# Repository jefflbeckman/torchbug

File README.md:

torchbug
========

Thingsquare application for LED poi

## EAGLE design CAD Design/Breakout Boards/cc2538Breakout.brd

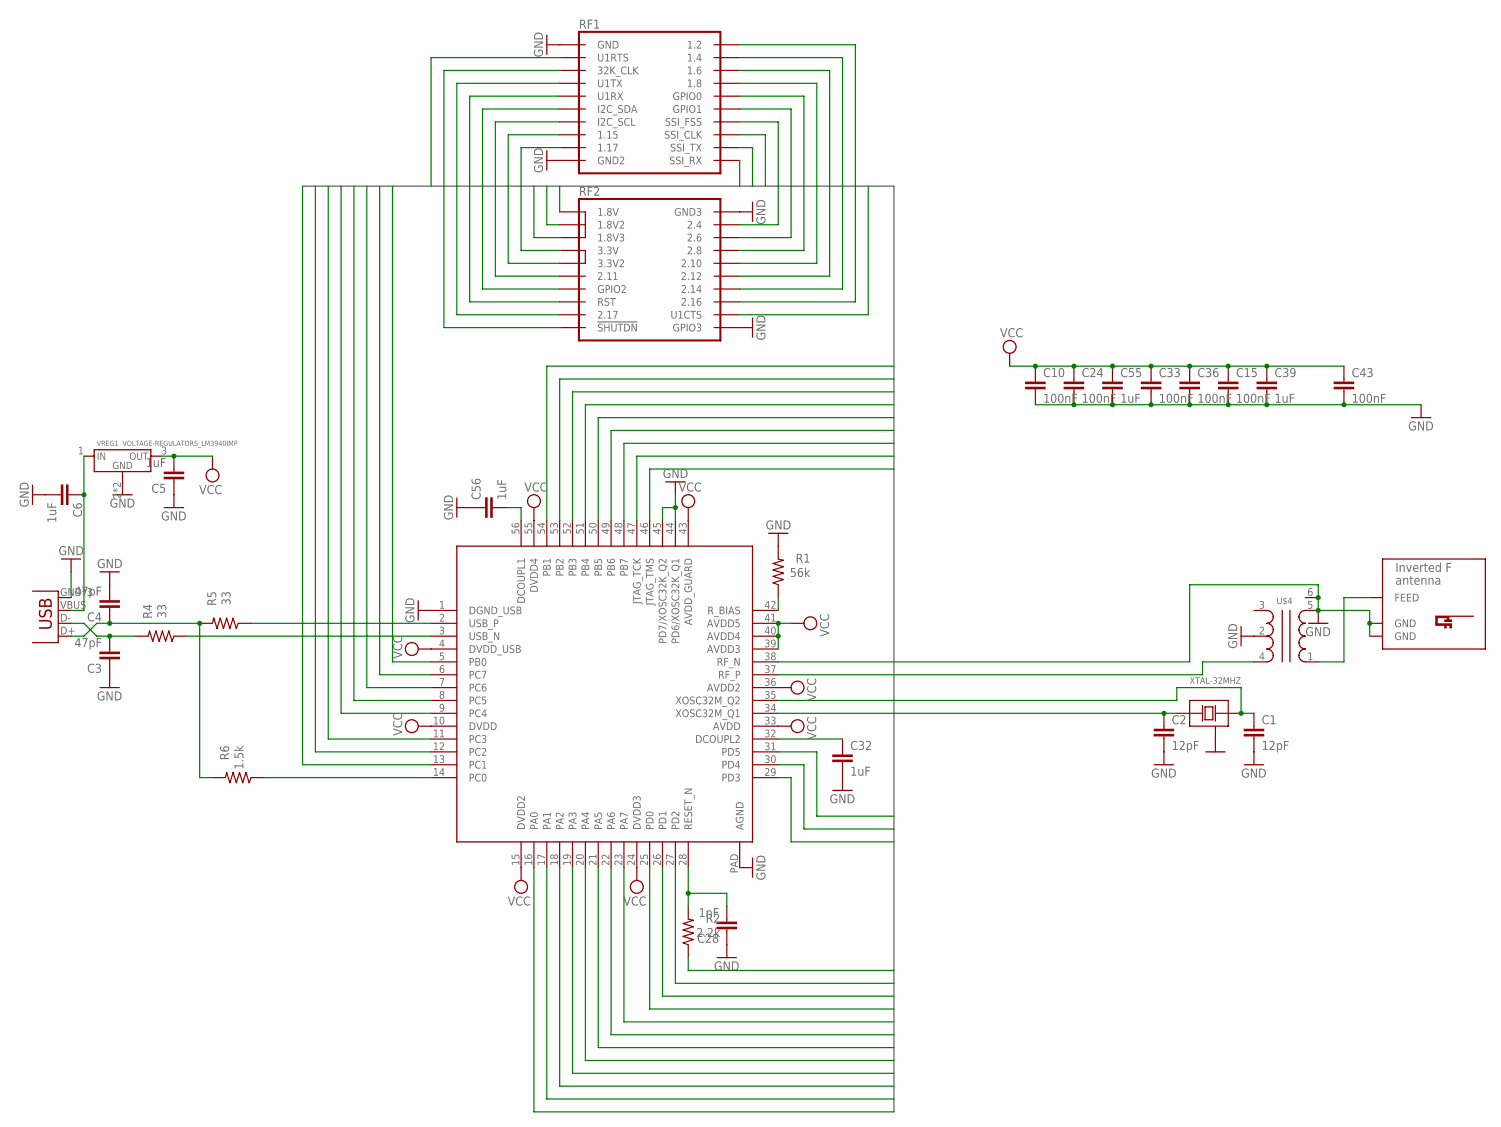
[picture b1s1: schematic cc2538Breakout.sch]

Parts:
C1, C2: 12pF; C0805
C3, C4: 47pF; C0805
C5, C6, C32, C39, C55, C56: 1uF; C0805
C10, C15, C24, C33, C36, C43: 100nF; C0805
C28: 1nF; C0805
JP1: USB-MICROB
R1: 56k; R0805
R2: 2.2k; R0805
R4, R5: 33; R0805
R6: 1.5k; R0805
U$1: CC2538; QFN56-EXT
U$2: ANTENNA_INVERTED_F_ANTENNA+0; ANTENNA_DN007+0
U$3: STELLARIS_LAUNCHPAD_EM_HEADERS; 2_EMHEADER_TOP
U$4: DISCRETE_BALUN; DISCRETE_BALUN-0805
VREG1: VOLTAGE-REGULATORS_LM3940IMP; VOLTAGE-REGULATORS_SOT223
XTAL-32MHZ: DISCRETE_XTAL-43225; DISCRETE_XTAL-4-3225

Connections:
ANT_GND: U$1.38 (RF_N), U$2.GND, U$2.GND@1 (GND), U$4.5, U$4.6
GND: C1.2, C2.2, C3.1, C4.2, C5.1, C6.2, C10.2, C15.2, C24.2, C28.1, C32.2, C33.2, C36.2, C39.2, C43.2, C55.2, C56.1, JP1.GND, JP1.MT1 (GND), JP1.MT2 (GND), R1.2, U$1.1 (DGND_USB), U$1.44 (PD6/XOSC32K_Q1), U$1.45 (PD7/XOSC32K_Q2), U$1.PAD (AGND), U$3.1 (GND), U$3.19 (GND2), U$3.22 (GND3), U$3.40 (GPIO3), U$4.2, VREG1.2 (GND), VREG1.4 (GND), XTAL-32MHZ.2 (GND1), XTAL-32MHZ.4 (GND1)
I/O2: U$1.12 (PC2), U$3.2 (1.2)
I/O3: U$1.5 (PB0), U$3.3 (U1RTS)
I/O4: U$1.11 (PC3), U$3.4 (1.4)
I/O5: U$1.54 (PB1), U$3.5 (32K_CLK)
I/O6: U$1.9 (PC4), U$3.6 (1.6)
I/O7: U$1.16 (PA0), U$3.7 (U1TX)
I/O8: U$1.8 (PC5), U$3.8 (1.8)
I/O9: U$1.17 (PA1), U$3.9 (U1RX)
I/O10: U$1.7 (PC6), U$3.10 (GPIO0)
I/O11: U$1.53 (PB2), U$3.11 (I2C_SDA)
I/O12: U$1.6 (PC7), U$3.12 (GPIO1)
I/O13: U$1.52 (PB3), U$3.13 (I2C_SCL)
I/O14: U$1.19 (PA3), U$3.14 (SSI_FSS)
I/O15: U$1.51 (PB4), U$3.15 (1.15)
I/O16: U$1.18 (PA2), U$3.16 (SSI_CLK)
I/O17: U$1.50 (PB5), U$3.17 (1.17)
I/O18: U$1.20 (PA4), U$3.18 (SSI_TX)
I/O20: U$1.21 (PA5), U$3.20 (SSI_RX)
I/O21: U$1.47 (JTAG_TCK), U$3.21 (1.8V)
I/O23: U$3.23 (1.8V2)
I/O24: U$1.46 (JTAG_TMS), U$3.24 (2.4)
I/O25: U$1.22 (PA6), U$3.25 (1.8V3)
I/O26: U$1.23 (PA7), U$3.26 (2.6)
I/O27: U$3.27 (3.3V)
I/O28: U$1.30 (PD4), U$3.28 (2.8)
I/O29: U$3.29 (3.3V2)
I/O30: U$1.31 (PD5), U$3.30 (2.10)
I/O31: U$3.31 (2.11)
I/O32: U$1.25 (PD0), U$3.32 (2.12)
I/O33: U$1.13 (PC1), U$3.33 (GPIO2)
I/O34: U$1.26 (PD1), U$3.34 (2.14)
I/O35: R2.1, U$3.35 (RST)
I/O36: U$1.27 (PD2), U$3.36 (2.16)
I/O37: U$1.49 (PB6), U$3.37 (2.17)
I/O38: U$1.29 (PD3), U$3.38 (U1CTS)
I/O39: U$1.48 (PB7), U$3.39 (!SHUTDN)
unnamed: C2.1, U$1.34 (XOSC32M_Q1), XTAL-32MHZ.1 (X1)
unnamed: U$2.FEED, U$4.1
unnamed: U$1.37 (RF_P), U$4.4
unnamed: C56.2, U$1.56 (DCOUPL1)
unnamed: C32.1, U$1.32 (DCOUPL2)
unnamed: R1.1, U$1.42 (R_BIAS)
unnamed: C28.2, R2.2, U$1.28 (RESET_N)
unnamed: R6.1, U$1.14 (PC0)
unnamed: R5.1, U$1.2 (USB_P)
unnamed: C3.2, JP1.D-, R4.2
unnamed: C4.1, JP1.D+, R5.2, R6.2
unnamed: R4.1, U$1.3 (USB_N)
unnamed: C6.1, JP1.VBUS, VREG1.1 (IN)
VCC: C5.2, C10.1, C15.1, C24.1, C33.1, C36.1, C39.1, C43.1, C55.1, U$1.4 (DVDD_USB), U$1.10 (DVDD), U$1.15 (DVDD2), U$1.24 (DVDD3), U$1.33 (AVDD), U$1.36 (AVDD2), U$1.39 (AVDD3), U$1.40 (AVDD4), U$1.41 (AVDD5), U$1.43 (AVDD_GUARD), U$1.55 (DVDD4), VREG1.3 (OUT)
XOSC32N_Q2: C1.1, U$1.35 (XOSC32M_Q2), XTAL-32MHZ.3 (X2)

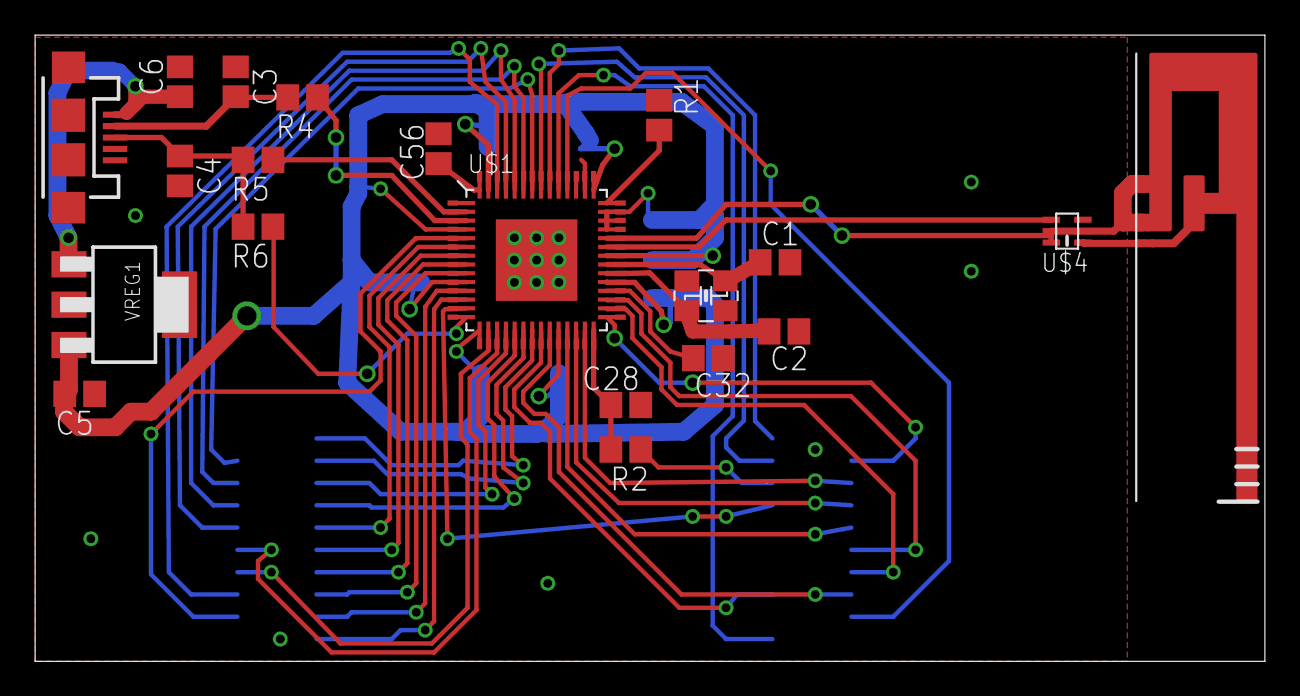
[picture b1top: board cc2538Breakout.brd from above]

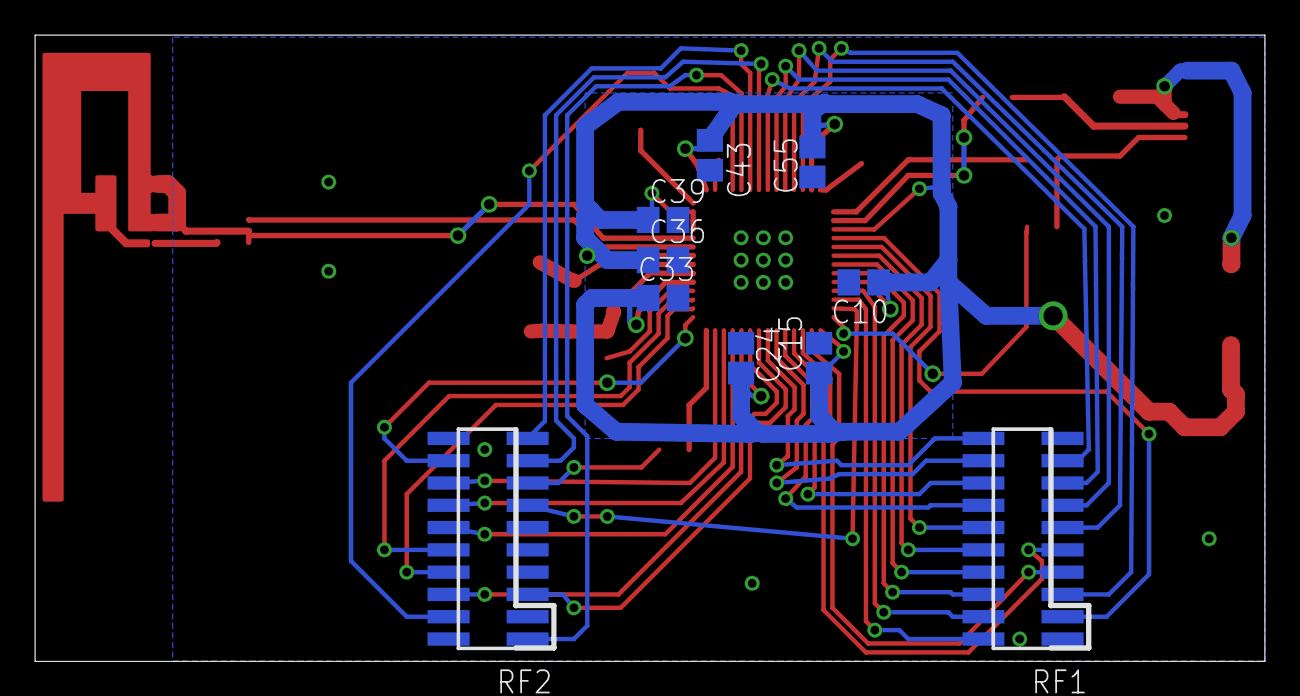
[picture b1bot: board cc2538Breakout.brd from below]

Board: 2 copper layers, 70.1 x 35.7 mm, 29 parts (9 on the bottom side), 49 nets.

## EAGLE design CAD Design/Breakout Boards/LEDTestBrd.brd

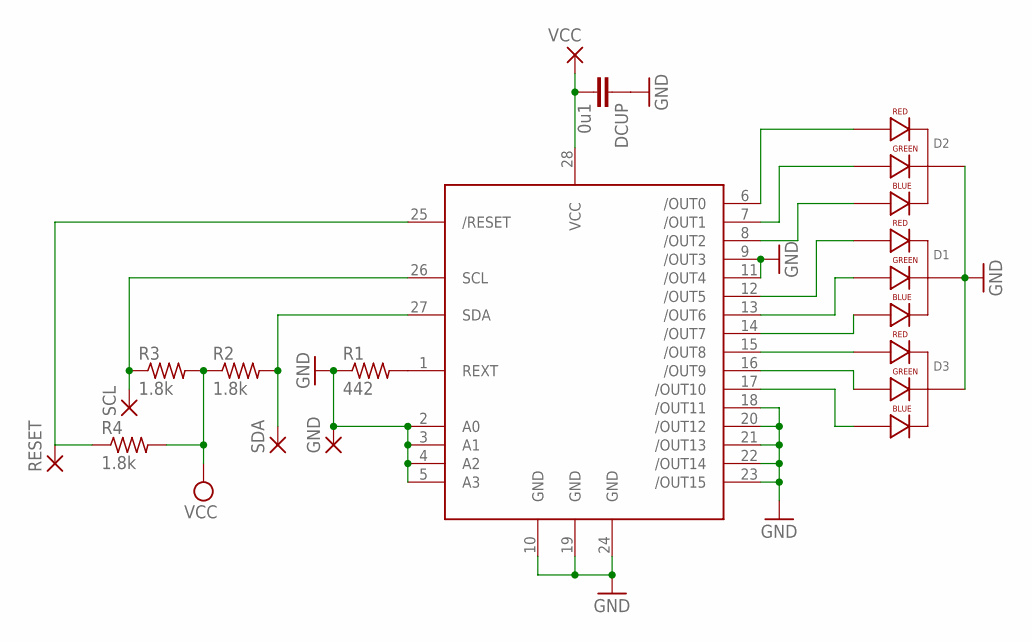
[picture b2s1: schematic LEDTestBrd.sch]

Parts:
D1, D2, D3: LED-RGB-CC-THRUCLEAR; LED-RGB-THRU
DCUP: 0u1; 0402-CAP
GND: 2,15/1,0
R1: 442; R0402
R2, R3, R4: 1.8k; R0402
RESET: 2,15/1,0
SCL: 2,15/1,0
SDA: 2,15/1,0
U$1: TLC59116; TSSOP28
VCC: 2,15/1,0

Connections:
GND: D1.2 (CATHODE), D2.2 (CATHODE), D3.2 (CATHODE), DCUP.1, GND.1, R1.1, U$1.2 (A0), U$1.3 (A1), U$1.4 (A2), U$1.5 (A3), U$1.9 (/OUT3), U$1.10 (GND), U$1.11 (/OUT4), U$1.18 (/OUT11), U$1.19 (GND), U$1.20 (/OUT12), U$1.21 (/OUT13), U$1.22 (/OUT14), U$1.23 (/OUT15), U$1.24 (GND)
unnamed: D1.1 (RED_CATHODE), U$1.12 (/OUT5)
unnamed: D2.1 (RED_CATHODE), U$1.6 (/OUT0)
unnamed: D2.3 (GREEN_CATHODE), U$1.7 (/OUT1)
unnamed: D2.4 (BLUE_CATHODE), U$1.8 (/OUT2)
unnamed: D1.3 (GREEN_CATHODE), U$1.13 (/OUT6)
unnamed: D1.4 (BLUE_CATHODE), U$1.14 (/OUT7)
unnamed: D3.1 (RED_CATHODE), U$1.15 (/OUT8)
unnamed: D3.3 (GREEN_CATHODE), U$1.16 (/OUT9)
unnamed: D3.4 (BLUE_CATHODE), U$1.17 (/OUT10)
unnamed: R1.2, U$1.1 (REXT)
RESET: R4.1, RESET.1, U$1.25 (/RESET)
SCL: R3.1, SCL.1, U$1.26 (SCL)
SDA: R2.2, SDA.1, U$1.27 (SDA)
VCC: DCUP.2, R2.1, R3.2, R4.2, U$1.28 (VCC), VCC.1

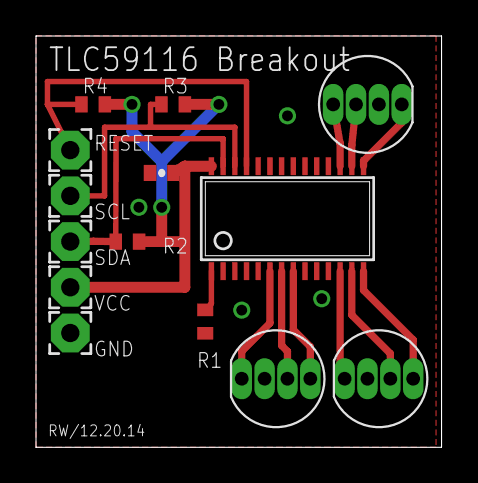
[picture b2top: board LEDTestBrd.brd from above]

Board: 2 copper layers, 22.5 x 22.9 mm, 14 parts (0 on the bottom side), 15 nets.

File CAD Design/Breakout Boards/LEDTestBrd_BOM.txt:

Partlist exported from /Users/Ryan/Documents/torchbug/CAD Design/Breakout Boards/LEDTestBrd.sch at 1/11/15 2:43 PM

Part  Value                Device               Package      Description                         PROD_ID  
D1    LED-RGB-CC-THRUCLEAR LED-RGB-CC-THRUCLEAR LED-RGB-THRU RGB Through-hole common cathode LED DIO-08418
D2    LED-RGB-CC-THRUCLEAR LED-RGB-CC-THRUCLEAR LED-RGB-THRU RGB Through-hole common cathode LED DIO-08418
D3    LED-RGB-CC-THRUCLEAR LED-RGB-CC-THRUCLEAR LED-RGB-THRU RGB Through-hole common cathode LED DIO-08418
DCUP  0u1                  CAP0402-CAP          0402-CAP     Capacitor                                    
GND                        2,15/1,0             2,15/1,0     THROUGH-HOLE PAD                             
R1    442                  R-US_R0402           R0402        RESISTOR, American symbol                    
R2    1.8k                 R-US_R0402           R0402        RESISTOR, American symbol                    
R3    1.8k                 R-US_R0402           R0402        RESISTOR, American symbol                    
R4    1.8k                 R-US_R0402           R0402        RESISTOR, American symbol                    
RESET                      2,15/1,0             2,15/1,0     THROUGH-HOLE PAD                             
SCL                        2,15/1,0             2,15/1,0     THROUGH-HOLE PAD                             
SDA                        2,15/1,0             2,15/1,0     THROUGH-HOLE PAD                             
U$1   TLC59116             TLC59116             TSSOP28                                                   
VCC                        2,15/1,0             2,15/1,0     THROUGH-HOLE PAD

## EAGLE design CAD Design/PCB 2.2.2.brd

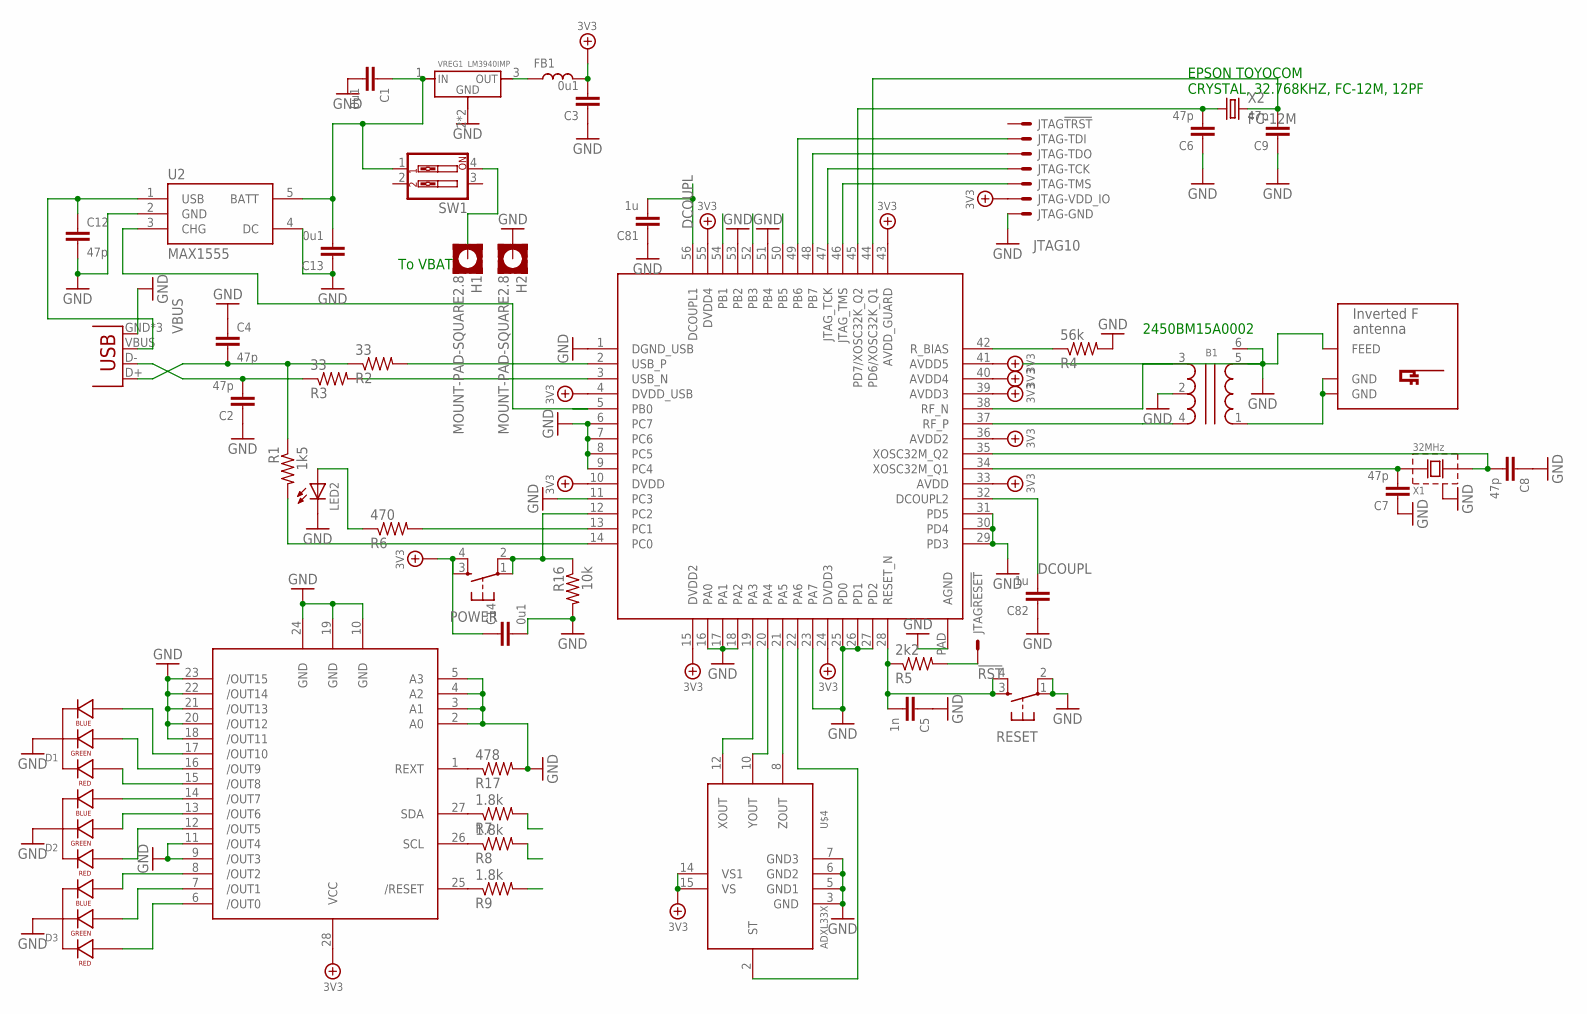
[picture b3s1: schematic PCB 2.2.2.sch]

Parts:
B1: BALUN; BALUN-0805
C1, C3, C13, C14: 0u1; C0402
C2, C4, C6, C7, C8, C9, C12: 47p; C0603
C5: 1n; C0402
C81, C82: 1u; C0402
D1, D2, D3: LED-RGB-CC-THRUDIFFUSE; LED-RGB-THRU
FB1: L0603; R603
H1, H2: MOUNT-PAD-SQUARE2.8; 2,8-PAD-SQUARE
JP1: USB-MICROB
JTAG: JTAG10; HDR-2X5-2.00
LED2: LED805; LED-805
POWER: TAC_SWITCHSMD; TACTILE_SWITCH_SMD
R1: 1k5; R0402
R2, R3: 33; R0402
R4: 56k; R0402
R5: 2k2; R0402
R6: 470; R0402
R7, R8, R9: 1.8k; R0402
R16: 10k; R0402
R17: 478; R0402
RESET: TAC_SWITCHSMD; TACTILE_SWITCH_SMD
SW1: SW_DIP-2; DIPSWITCH-02
U1: CC2538; QFN56
U2: MAX1555; SOT23-5
U$2: INVERTED_F_ANTENNA+0; DN007+0
U$3: TLC59116; TSSOP28
U$4: ADXL33X; 16LCSP
VREG1: LM3940IMP; SOT223
X1: 32MHz; XTAL-4-3225
X2: FC-12M

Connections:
3V3: C3.2, C14.1, FB1.2, JTAG.1, JTAG.2, POWER.3, POWER.4, U1.4 (DVDD_USB), U1.10 (DVDD), U1.15 (DVDD2), U1.24 (DVDD3), U1.33 (AVDD), U1.36 (AVDD2), U1.39 (AVDD3), U1.40 (AVDD4), U1.41 (AVDD5), U1.43 (AVDD_GUARD), U1.55 (DVDD4), U$3.28 (VCC), U$4.14 (VS1), U$4.15 (VS); also elsewhere on the board
!RST: JTAG.4, R5.2
!RST_PIN: C5.2, R5.1, RESET.3, RESET.4, U1.28 (RESET_N)
ACCRESET: R9.2, U1.54 (PB1)
ACCSCL: R8.2, U1.52 (PB3)
ACCSDA: R7.2, U1.50 (PB5)
CN1: C4.2, JP1.D+, R1.1, R2.1
DCOUPL: C81.2, C82.2, U1.32 (DCOUPL2), U1.56 (DCOUPL1)
GND: B1.2, B1.5, B1.6, C1.2, C2.1, C3.1, C4.1, C5.1, C6.1, C7.1, C8.1, C9.1, C12.2, C13.1, C14.2, C81.1, C82.1, D1.2 (CATHODE), D2.2 (CATHODE), D3.2 (CATHODE), H2.B2,8, JP1.GND, JP1.MT1 (GND), JP1.MT2 (GND), JTAG.8, JTAG.10, LED2.C, R4.2, R16.2, R17.2, RESET.1, RESET.2, U1.1 (DGND_USB), U1.6 (PC7), U1.7 (PC6), U1.8 (PC5), U1.9 (PC4), U1.11 (PC3), U1.16 (PA0), U1.18 (PA2), U1.23 (PA7), U1.25 (PD0), U1.26 (PD1), U1.27 (PD2), U1.29 (PD3), U1.30 (PD4), U1.31 (PD5), U1.51 (PB4), U1.53 (PB2), U1.PAD (AGND), U2.2 (GND), U2.4 (DC), U$2.FEED, U$3.2 (A0), U$3.3 (A1), U$3.4 (A2), U$3.5 (A3), U$3.9 (/OUT3), U$3.10 (GND), U$3.11 (/OUT4), U$3.18 (/OUT11), U$3.19 (GND), U$3.20 (/OUT12), U$3.21 (/OUT13), U$3.22 (/OUT14), U$3.23 (/OUT15), U$3.24 (GND), U$4.3 (GND), U$4.5 (GND1), U$4.6 (GND2), U$4.7 (GND3), VREG1.2 (GND), VREG1.4 (GND), X1.2 (GND1), X1.4 (GND1)
unnamed: R2.2, U1.2 (USB_P)
unnamed: R3.2, U1.3 (USB_N)
unnamed 11: POWER.1, POWER.2, R16.1, U1.12 (PC2); also elsewhere on the board
unnamed: R1.2, U1.14 (PC0)
unnamed: R4.1, U1.42 (R_BIAS)
unnamed: JTAG.9, U1.47 (JTAG_TCK)
unnamed: JTAG.7, U1.46 (JTAG_TMS)
unnamed: U1.21 (PA5), U$4.8 (ZOUT)
unnamed: U1.20 (PA4), U$4.10 (YOUT)
unnamed: U1.19 (PA3), U$4.12 (XOUT)
unnamed: C1.1, C13.2, SW1.1, U2.5 (BATT), VREG1.1 (IN)
unnamed: C2.2, JP1.D-, R3.1
unnamed: H1.B2,8, SW1.4
unnamed: D3.1 (RED_CATHODE), U$3.6 (/OUT0)
unnamed: D3.3 (GREEN_CATHODE), U$3.7 (/OUT1)
unnamed: U1.22 (PA6), U$4.2 (ST)
unnamed 25: FB1.1, VREG1.3 (OUT); also elsewhere on the board
unnamed: D3.4 (BLUE_CATHODE), U$3.8 (/OUT2)
unnamed: R17.1, U$3.1 (REXT)
unnamed: D1.1 (RED_CATHODE), U$3.15 (/OUT8)
unnamed: U1.5 (PB0), U2.3 (CHG)
unnamed: D1.3 (GREEN_CATHODE), U$3.16 (/OUT9)
unnamed: C6.2, U1.45 (PD7/XOSC32K_Q2), X2.1
unnamed: D2.1 (RED_CATHODE), U$3.12 (/OUT5)
unnamed: D1.4 (BLUE_CATHODE), U$3.17 (/OUT10)
unnamed: D2.3 (GREEN_CATHODE), U$3.13 (/OUT6)
unnamed: B1.3, U1.38 (RF_N)
unnamed: B1.4, U1.37 (RF_P)
unnamed: D2.4 (BLUE_CATHODE), U$3.14 (/OUT7)
unnamed: C8.2, U1.35 (XOSC32M_Q2), X1.3 (X2)
unnamed: C7.2, U1.34 (XOSC32M_Q1), X1.1 (X1)
unnamed: C9.2, U1.44 (PD6/XOSC32K_Q1), X2.2
unnamed: LED2.A, R6.1
unnamed: R6.2, U1.13 (PC1)
unnamed: R7.1, U$3.27 (SDA)
unnamed: R8.1, U$3.26 (SCL)
unnamed: R9.1, U$3.25 (/RESET)
PB6: JTAG.5, U1.49 (PB6)
PB7: JTAG.6, U1.48 (PB7)
RF: B1.1, U$2.GND, U$2.GND@1 (GND)
VBUS: C12.1, JP1.VBUS, U2.1 (USB)

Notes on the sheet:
EPSON TOYOCOM CRYSTAL, 32.768KHZ, FC-12M, 12PF
2450BM15A0002
To VBAT

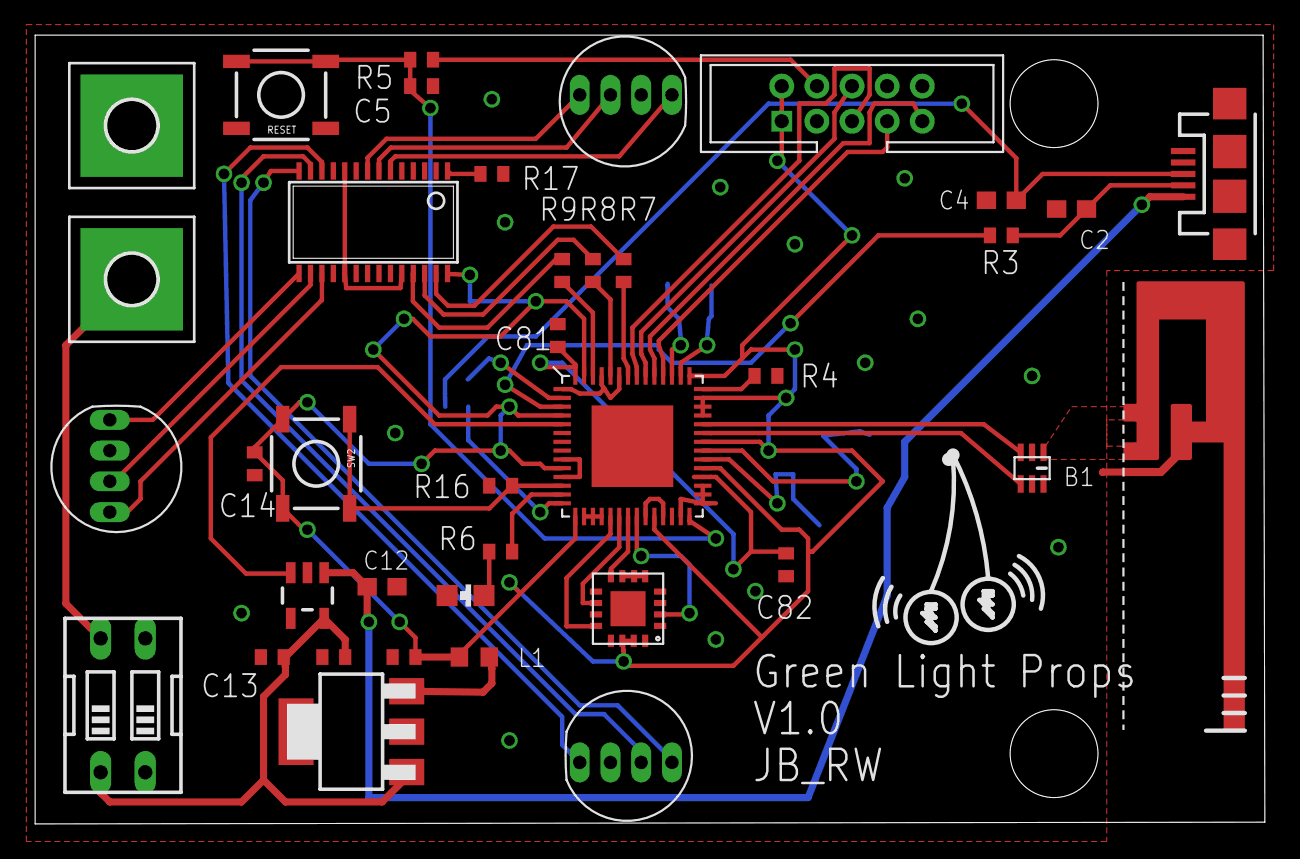
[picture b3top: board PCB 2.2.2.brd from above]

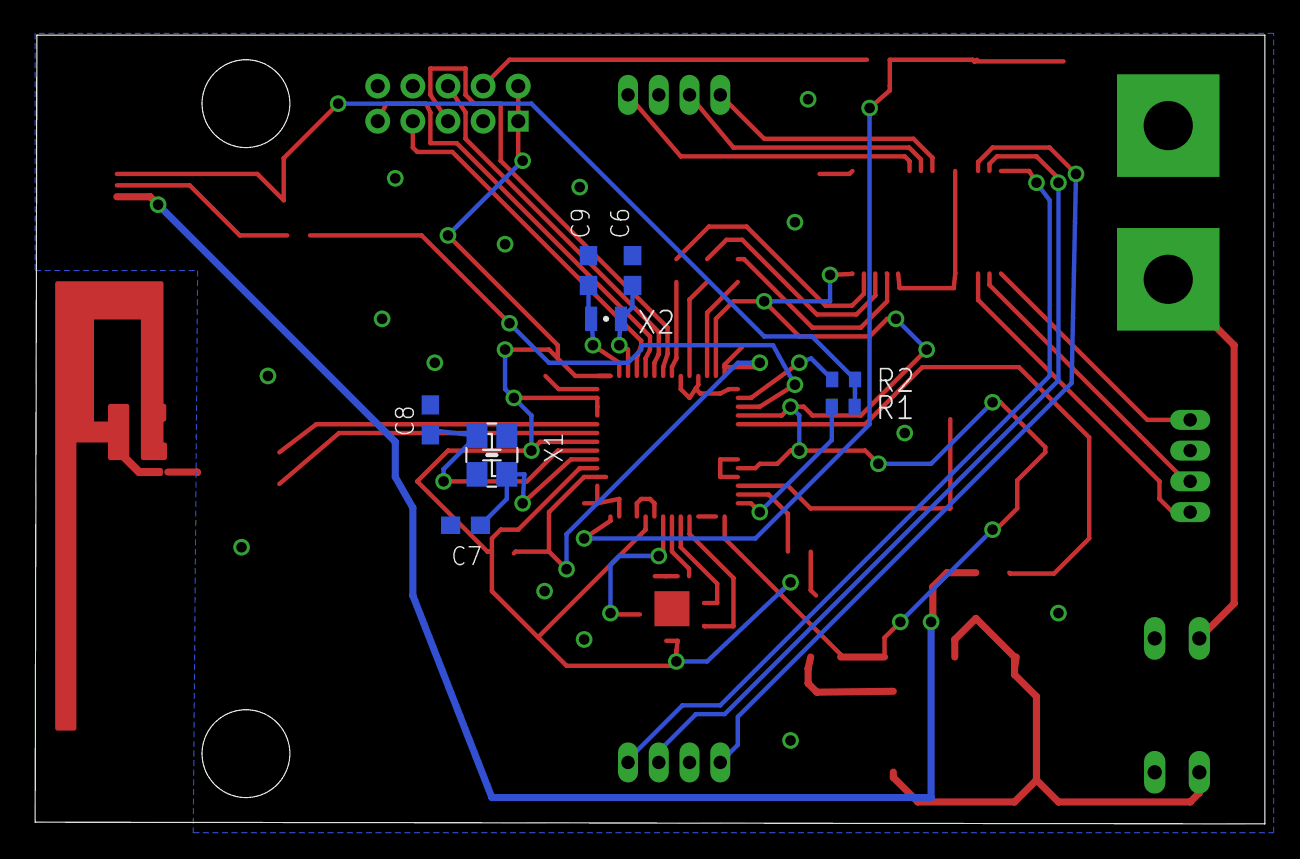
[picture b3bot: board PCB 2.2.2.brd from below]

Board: 2 copper layers, 70.0 x 44.9 mm, 46 parts (8 on the bottom side), 50 nets.

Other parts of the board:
L1: R603
SW2: TACTILE_SWITCH_SMD

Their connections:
3V3: L1.2, SW2.3, SW2.4; also elsewhere on the board
unnamed 11: SW2.1, SW2.2; also elsewhere on the board
unnamed 25: L1.1; also elsewhere on the board

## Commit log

2013-11-27 CC2538QFN eagle library
2014-02-23 Initial Sync
    Accelerometer placed, ready for IC.
2014-02-24 Schematic Update
    Added Antennae, charger IC, reset switch
2014-02-24 Schematic major version update
    Added LEDs
2014-03-01 Added 50 ohm resistors to LEDs on board.
2014-03-01 Updated resistor values
2014-03-02 Schematic clean up
    Major version update. Added power switch, uniform resistors. Now going
    to fresh board.
2014-03-02 Schematic clean up for real.
    Added power switch, uniform resistors. Major version ready for board.
2014-03-02 Schematic Update, board push
    Replaced some capacitors, 2.1 board with preliminary element placement
2014-03-02 Schematic Update
    Removed decoup bank, push for bill of mats.
2014-03-03 Board update
    Added Vbatt pads, ground plane, ready to route
2014-03-03 3/2 Final push
    Attempted autoroute. Need to reorganize board.
2014-03-09 Routing Day Two
    Increased board size, rearranged components, ~60% autoroute so far.
2014-03-10 End of day 3/9/14
    Tried migrating components to bottom, routing attempts failed.
2014-03-16 3/16/14 AM fixes
    Tweaked schematic as per Jeff’s audit. Begun re-orienting parts on
    board.
2014-03-16 Midday Push
    Manual routing ~50% complete. Needs new accelerometer, yet to
    integrate LED driver.
2014-03-16 Major Version Update
    2.2.0: New accelerometer, LED driver, board ~90% routed
2014-03-17 Test commit
    troubleshooting
2014-03-17 End of day Commit
    v2.2 schematic, board 99% routed
2014-03-17 Preliminary board audit
    Finished preliminary routing, begun ripping up erroneous traces.
2014-03-22 Minor version update
    Initial routing 100% complete on 2.2.1, reviewing DRC errors.
2014-03-23 Correction
    Correcting 2.2.1 with most current save
2014-03-23 Changed thruhole LED width to accomodate design rules
2014-03-23 Ready to order PCB Update
    labeled, optimized, and DRC’d. Board ready to order!
2014-03-24 Final board edit 1
    minor rerouting for consistency, GND bias added for ground plane
    integrity.
2014-04-24 Version Update - 2.5
    Cleaned up Schematic for part placement reference. SW1 to be modified.
2014-04-24 Changed dipswitch to reflect the switch that we ordered
2014-12-15 Test Board Circuit Design
    Created ACC and LED circuits for individual test boards.
2014-12-20 Did I unbreak it yet?
    derp-hub
2014-12-20 Cleaning
2014-12-20 LEDBreakout Upload
    v1 Breakout board for tlc59116.
2014-12-23 AccBreakout, LEDbrkout rev1
    Revised TLC59116 breakout (names/resistors), uploaded ADXL33X breakout
    board.
2015-01-11 First breakout board design review
    Minor changes to silkscreens, added documentation. Acc. and LED driver
    boards ready for board house.
2015-01-12 Power Circuit Breakout Upload
    Power circuit breakout board ready to go to board house. Datasheets
    for LM3940 and MAX1555 included.
2015-01-14 add a readme
    test on Adrian's computer
2015-01-14 adding a blender model for the core
2015-02-02 cc2538 start push
2015-02-02 cc2538 breakout
2015-02-22 cc2538EM schematic finished
    Pin matched headers, added VCC decoupling bank. Ready for board layout.
2015-05-22 cc2538 Breakout, Board Layout upload1
    Partial routing on microprocessor breakout, fixed wiring in antennae.
2015-05-22 cc2538 breakout. update#2
    Routed antennae, better xtal routing. Most of power routed. I/O still
    to come.
2015-06-12 Commit for console switching
    Moving latest changes to desktop
2015-06-15 Resyncing on desktop to recover .BRD file
    .BRD file corrupted after last work session. Sadness ensued.
2015-06-15 Cautious Sync
    Upload of local copy of .BRD file, rerouting I/O pins.
2015-06-15 Routing, First DRC complete
    cc2538 Breakout ready for design review and final ERC/DRC checks.
2015-06-16 cc2538 Breakout_rev1.0
    cc2538 Breakout board ready to go to print. Fixed crossed signals on
    PC0/PC1, verified headers, second and third DRC’s passed.

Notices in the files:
parts and their libraries:
SparkFun-LED: Licensing: Creative Commons ShareAlike 4.0 International - https://creativecommons.org/licenses/by-sa/4.0
